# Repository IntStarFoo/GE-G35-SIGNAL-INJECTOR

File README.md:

GE-G35-SIGNAL-INJECTOR
======================

A board layout that enables an easy process for tapping into the POWER, GROUND, SIGNAL wires in a GE G35 LED light set.  The goal is to create a simple, safe and switchable link between the original signal a new signal produced by whatever proc is plugged in.  And Stuff.

I give no guarantees of safety or function.  Use at your own risk.

<h3>Feature Considerations</h3>
The main goal is to be able to leave the original operation features intact with the option of physically switching the signal over to the output from your own MCU.  

I wanted to stick to a single sided, single layer design so people could more easily manufacture the board at home, but it may be a bit too complex for that.  If there is an option to sending the layout to an online board house and ordering 3 or 4 for a reasonable price, that works too.

<h4>Basic 2 way switch</h4>
Position 1 completely disconnects the additional MCU and routes the signal from the original controller to the signal line running through the bulbs.  
Position 2 completely disconnects the original signal from the original controller and replaces it with a the signal coming from a pin on the additional MCU.
<h5>Possible Additional Features</h5>
There may also be a case where someone wants to intercept the signal from the original controller and feed it into the additional MCU for further processing.  I'm not sure if this should be an additional position on the mechanical switch or connected via a jumper.
There may also be a case where someone wants to use a relay in place of the mechanical switch.  If it's possible to design the PCB in such a way that the switch option and relay option are available, then great. 

<h3>Physical Layout Considerations</h3>
I've been thinking about ways to simplify installation onto a set of lights.   I am a little apprehensive about this part because of the possibility for someone to incorrectly attach the wires.  This connector design might also be helpful for replacing / removing bad bulbs. That process is a pain and currently requires cutting out the section containing the bad bulb and reconnecting the two bare ends.

I configured this for the MSP430.  I'm not sure how popular the 20 pin style MCU socket is and how common it is to have the 3 connections required (ground, power, signal) located in the pin positions.  Thoughts and feedback here are much needed.

Options include: 

1. A crimp-on tap connector similar to an automotive wire tap.  The tap connector would have to perform an additional, advanced maneuver where it actually severs the middle (signal) line as it is crimped on.  Also, there would have to be some method for dealing with crimping it on in either direction. (V+, Signal, GND) vs (GND, Signal, V+).  I believe there are some simple circuits that could auto correct for polarity.  

2.  A PCB with screw block connectors and wire holders (see drawing below).

A suggestion was made to make the input and output screw terminal positions... _"pcb routing might be a little easier with the screw terminals side by side, especially if you're willing to reverse the wire order, which it seems you are."_

Current Schematic (Last updated by svenstucki)<br/> 

Current Layout (Last updated by svenstucki)<br/>

Example Board Completed (with scrap parts)<br/>
<br/>
<br/>

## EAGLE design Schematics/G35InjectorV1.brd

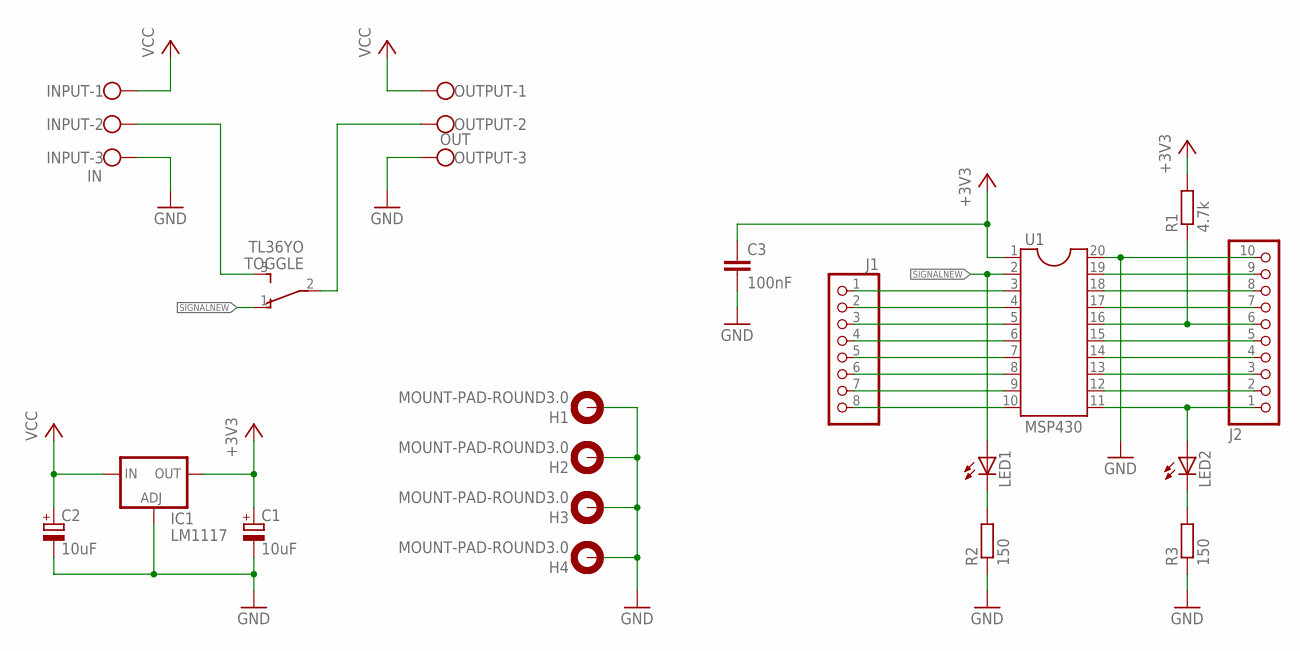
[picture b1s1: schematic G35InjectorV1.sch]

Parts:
C1, C2: 10uF; E5-10,5
C3: 100nF; C0805
H1, H2, H3, H4: MOUNT-PAD-ROUND3.0; 3,0-PAD
IC1: LM1117; 317TS
INPUT: IN; W237-103
J1: PINHD-1X8; 1X08
J2: PINHD-1X10; 1X10
LED1, LED2: LED5MM
OUTPUT: OUT; W237-103
R1: 4.7k; R0805
R2, R3: 150; R0805
TOGGLE: TL36YO; TL3XYO
U1: MSP430; SOCKET-20

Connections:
+3V3: C1.+, C3.1, IC1.2 (OUT), R1.2, U1.1
GND: C1.-, C2.-, C3.2, H1.B3,0, H2.B3,0, H3.B3,0, H4.B3,0, IC1.1 (ADJ), INPUT.3, J2.10, OUTPUT.3, R2.1, R3.1, U1.20
unnamed: J1.1, U1.3
unnamed: J1.2, U1.4
unnamed: J1.3, U1.5
unnamed: J1.4, U1.6
unnamed: J1.5, U1.7
unnamed: J1.6, U1.8
unnamed: J1.7, U1.9
unnamed: J1.8, U1.10
unnamed: J2.9, U1.19
unnamed: J2.8, U1.18
unnamed: J2.7, U1.17
unnamed: J2.6, R1.1, U1.16
unnamed: J2.5, U1.15
unnamed: J2.4, U1.14
unnamed: J2.3, U1.13
unnamed: J2.2, U1.12
unnamed: J2.1, LED2.A, U1.11
unnamed: INPUT.2, TOGGLE.3 (S)
unnamed: OUTPUT.2, TOGGLE.2
unnamed: LED1.K (C), R2.2
unnamed: LED2.K (C), R3.2
SIGNALNEW: LED1.A, TOGGLE.1 (O), U1.2
VCC: C2.+, IC1.3 (IN), INPUT.1, OUTPUT.1

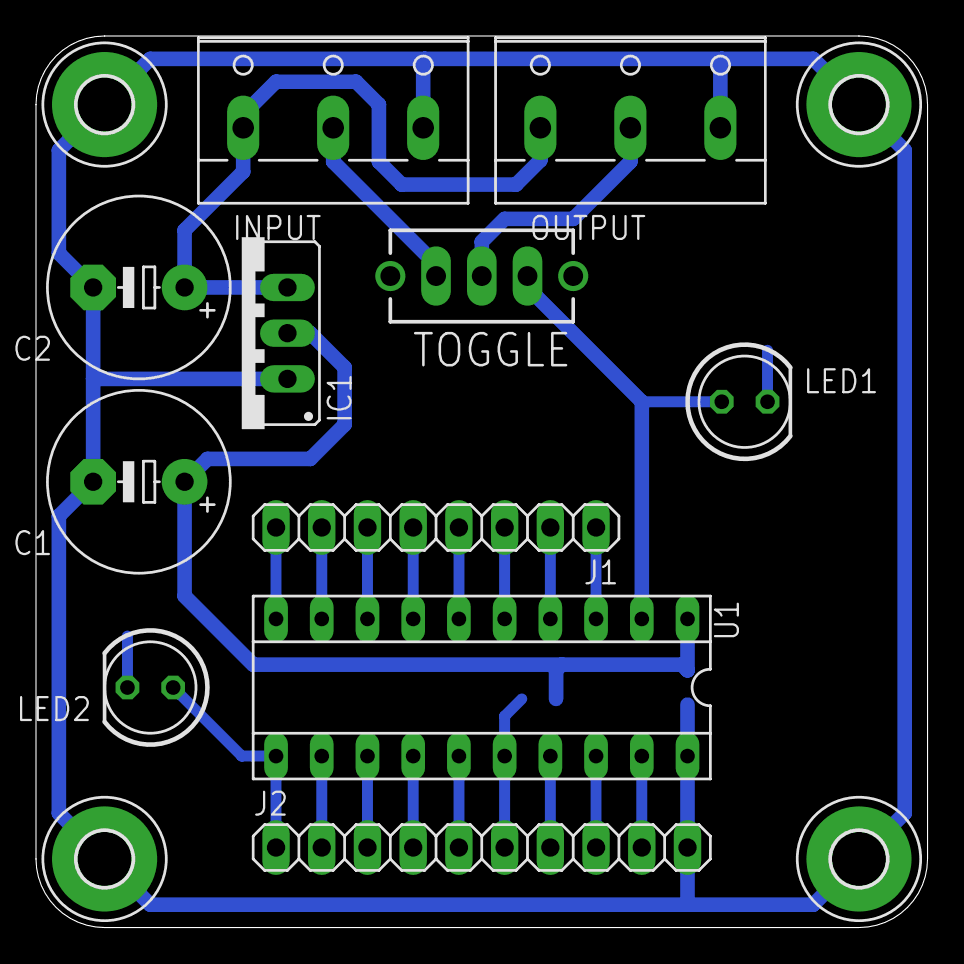
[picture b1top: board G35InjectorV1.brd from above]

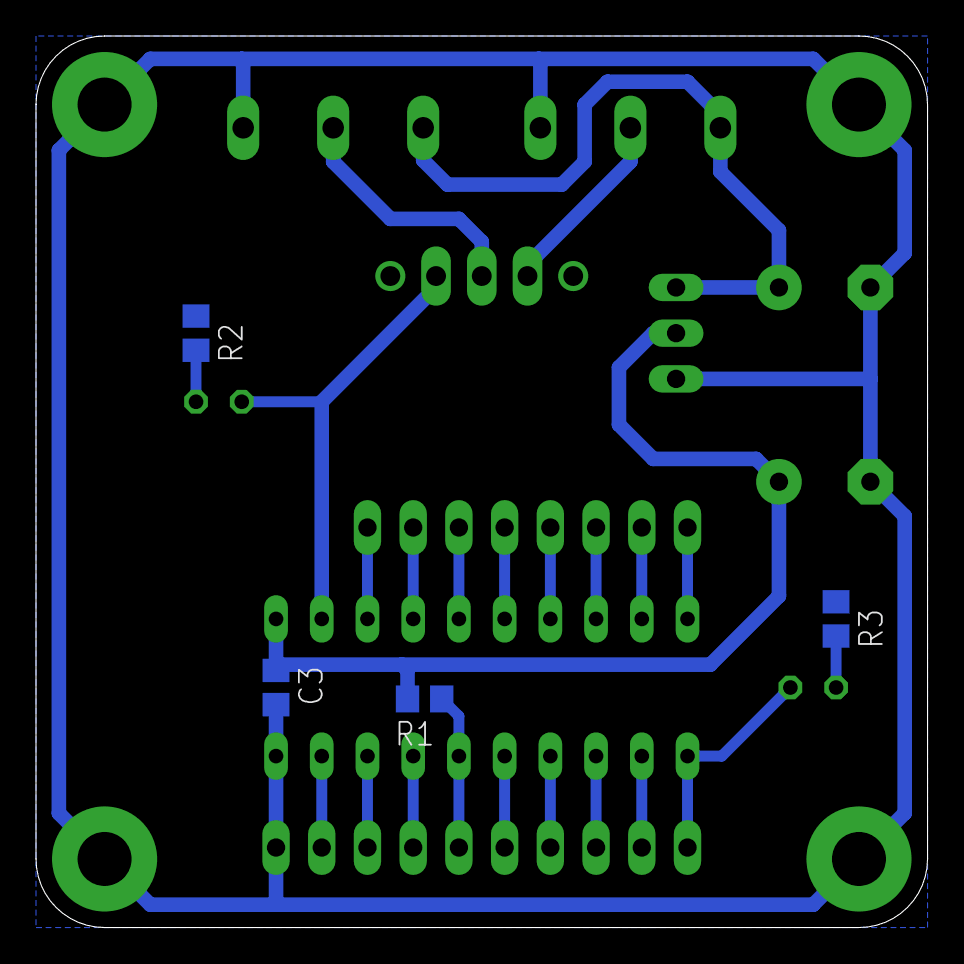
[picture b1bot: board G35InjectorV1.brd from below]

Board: 2 copper layers, 49.5 x 49.5 mm, 19 parts (4 on the bottom side), 25 nets.

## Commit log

2014-11-22 Adding Schematic
    This is my first attempt at a schematic.
2014-11-23 Fixed existing schematic
2014-11-23 Added routed single-side PCB
2014-11-24 Update README.md
    Updating based on great contributions from svenstucki. Thanks!
2015-01-20 Update README.md
    Added pictures of completed board, spelling, content
